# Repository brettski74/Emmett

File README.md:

# Emmett KiCad Plugin

Welcome to the Emmett Element Router - a comprehensive helper for routing heating element traces.

If you're looking for some way to control your hotplate, maybe [Milton](https://github.com/brettski74/Milton) can help.

Join us on [Discord](https://discord.gg/dnQJEGFCZ9) to meet other people interested in DIY solder reflow hotplates, ask questions, make suggestions or discuss problems. You can also raise issues here and I'll take a look when I can.

# Features

- Supports single-sided Aluminium PCB layouts.
- Includes DIY thermal fuse in the layout for safety.
- Allows resizing of the board to suit requirements.
- Performs basic thermal calculations to determine feasibility of proposed design.
- Calculates optimal resistance values based on power, temperature and voltage requirements of the hotplate.
- Optimize track geometry to achieve desired resistance value.
- Opens a dialog for entering heating element design parameters
- Allowance for process variability in copper thickness and minimum clearances.

# Requirements

- KiCad 9.0 or later
- Python 3.6+ (included with KiCad)

**NOTE: This plugin is built using the Python SWIG API for KiCad which has been deprecated by the KiCad development team. Support for the SWIG API may be removed in KiCad 10 or a later version of KiCad, at which time this plugin will cease to work as it is currently written.**

# Installing Emmett

1. Download the release ZIP file (eg. emmett-1.0.0.zip)
2. Open KiCad
3. Launch the Plugin and Content Manager
4. Click the *Install from File...* button.
5. Select the release ZIP file you downloaded (eg. emmett-1.0.0.zip)

You should now see Emmet show up among your installed plugins. When you open KiCad, you should see a new button on the tool bar for launching the Emmett dialog.

# Using Emmett

Emmett is designed to work with purpose-designed PCB layouts for heating elements. The current version only supports a single layout algorithm for an aluminium hotplate design of mine. It includes a thermal fuse which you must create on the manufactured boards for them to work and has surface mount pads for power connection. The fuse link and power connections must be soldered in place using a higher temperature solder alloy. Despite the presence of the thermal fuse and the use of higher temperature solder alloys, there is a risk that your live power connections reflow and the cables become loose. This may pose a risk of fire or equipment damage.

**It is important to ensure that your hotplate assembly includes precautions to limit the movement of the live cable ends should they become detached during a fault or other unintended modes of operation.**

You can find a hotplate layout that works with Emmett in the releases.

Load the hotplate layout.
Click the Emmett button on the toolbar to launch Emmett.

When you first open Emmett, he will analyze the currently open PCB layout to deduce some parameter values from it. On the *Technical* tab, you set most of the relevant design parameters for creating your hotplate.

## Electrical Specifications

The most likely parameters you may wish to change are the voltage and power capabilities of your power supply. These will determine the ideal resistance of the heating element on your hotplate. The *Target Resistance* will normally be calculated based on the voltage and power you provide, but you can manually enter a value if you desire.

The *Cold Current* value shows how much current will be required at ambient temperature to produce the required power in your heating element. This can give you some idea of how current constrained the design may be at low temperatures.

### Specifying Voltage and Power

Power applied to the hotplate is what matters most for achieving certain temperatures and rates of heating. You should let the thermal specifications guide the power requirements for your hotplate. If you have power to burn, you can increase the power and power margin to your heart's content, but excessive power won't really help that much. Depending on your control strategy, extremely excessive power could pose controllability problems.

Voltage is a different matter. The following advice assumes that your power supply has some way of limiting the current to safe levels regardless of the load of the current voltage and current set points. If you're power constrained, then your best bet is to specify the maximum voltage that your power supply can handle. The heating element resistance will increase with temperature. Because of this, you will be current constrained at low temperatures and voltage constrained at high temperatures. You want to take advantage of the maximum power into your hotplate at reflow temperatures because that is where the effects of thermal leakage to the ambient will be the highest and therefore you'll need the most power there to keep increasing temperature. If you are not power constrained and have the ability to vary the voltage applied to the hotplate, you may want to select a lower operating voltage. The *Cold Current* field will show the current required to reach your design power when the hotplate is at ambient temperature. Ideally you would select an operating voltage that produces a cold current value that is within the current output limits of your power supply.

## Thermal Specifications

The *Thermal Specifications* can also be tailored to your needs. All of the parameters in this section ultimately affect how much power we assume will be needed by your hotplate design to perform.

For standard tin-lead solders that melt at around 183°C, the standard temperature settings or 220°C and 25°C should be sufficient. If you're worried about tripping your thermal fuse or wear and tear on your board, you can run it at a lower temperature but unless you are seriously power constrained (eg. below 30% power margin) it is probably best to leave the maximum temperature at 220°C.

*Thermal Resistance* provides a measure of how quickly and easily your hotplate assembly loses heat to the surrounding environment. Technically, this is the thermal resistance from your hotplate assembly to the ambient environment. The lower this value, the faster heat leaks into the surrounding environment, which means that it requires more power just to resist the natural cooling from convection, conduction and radiation. This value will be estimated based on the dimensions of your hotplate. The formula used for this is somewhat speculative and based on a limited amount of empirical data. Your mileage may vary.

*Power Margin* is a somewhat arbitrary factor relating how much power you need to hold the hotplate at it's maximum temperature versus how much power is available to drive the hotplate. To heat the hotplate and its load up quickly, you need substantially more than just the holding power. A power margin of 100% is recommended. This basically sets the power requirement for your hotplate to double the holding power (ie. the holding power + 100% of the holding power on top of that). Values below about 25% may be sluggish and may struggle to reach the desired reflow temperatures in the available time unless you modify your reflow profiles to be much longer than are typical. Even at a power margin of 25-30% you may need to increase the length of your profile by 50-100% in order to give the hotplate long enough to heat up to the required temperatures to form good solder joints. 100% is a good target that should allow your hotplate to reach reflow temperatures in times comparable to standard reflow profiles.

## Track Specifications

*Minimum Spacing* sets the minimum distance between the adjacent edges of adjacent tracks - ie. the width of the non-conductive space between adjacent tracks. 0.2mm is a fairly safe and conservative value that should work for most PCB manufacturers. There's probably no need to go smaller.

*Track Thickness* sets the thickness of the copper layer that will be on your finished PCB. For 1oz copper, this should be 35µm, although it's possible that with different manufacturers or even different batches from the same manufacturer it could vary. If you've ordered PCB hotplates before, you'll know that the resistance of the manufactured PCBs does not always match the theoretical calculations. It's difficult for me to say why this is. It could be due to a variety of possible causes including a thinner than expected copper layer, etching undercut (ie. narrower than expected traces), oxidation or impurities in the copper... Who knows? Without expensive test and measurement equipment I cannot say for sure. Whatever the reason, if you're finding that the resistance of your manufactured PCB heaters is wildly different from expected, this is a parameter that you can use to adjust the calculations, spin up a new board and have that manufactured to hopefully meet your resistance expectations.

*Track Material*... It's possible that PCB hotplates could be manufactured using a conductive material other than copper. While I've given some thought to this possibility, it seems unlikely for there to be other options for DIYers at this time, so I've forgone the effort to implement support for other materials at this time. If this situation should change, maybe we can update Emmett to know about other material properties. This version explicitly uses the published values for copper.

## Track Geometry

*Track Width* is the width in millimetres of the tracks that will be created for your heating element. Narrower tracks produce higher resistances. Wider tracks produce lower resistances. Ideally, you would allow the form to calculate the optimal value for this for you based on the thermal and electrical specifications you've provided, but if you want, you can manually enter a value here instead. You do you!

*Track Spacing* is the width of the non-conductive space between adjacent edges of adjacent tracks. Ideally we want to keep this as small as possible. Wider tracks are more durable and have better thermal coupling to the underlying substrate, both of which are desirable.

*Track Pitch* is the centre to centre measurement for adjacent tracks. Track pitch is what determines how many tracks can fit within a given width on the board. It is the sum of the track width and track spacing.

## Board Extents

The *Left*, *Top*, *Right* and *Bottom* values show the position of the edges of the board as defined by the edge cuts layer on your PCB. This is determined during board analysis and the values are read-only.

*Width* and *Height* show the width and height of the layout in millimetres. This is again derived from the edge cuts layer. Width is the difference of the right and left values. Height is the difference of the bottom and top values. They are editable, but changes to these values have no effect unless you click the *Resize* button. If you wish to change the size of your hotplate, you can modify the width and height values here and then click the *Resize* button. You should see the edge cuts and mounting holes move to create a layout with your new dimensions. Doing this will also automatically trigger a re-analysis of the board layout but will not trigger regeneration of the heating element tracks.

## Electrical

This shows the calculated values of the heating element resistance at ambient temperature (ie. *Cold Resistance*) and at the maximum operating temperature (ie. *Hot Resistance*). These are calculated during board analysis and after generation of new tracks.

## Buttons

*Load* Not currently implemented. The intention was to save the parameters to a file that could be loaded again later, but board analysis seems to make this moot. i may remove these buttons in a future version. For the moment, this does nothing when clicked.

*Save* Not currently implemented. See *Load*.

*Analyze* Initiate a new analysis of the board and update the parameters accordingly. This can be used to effectively revert all the edits that have been made on the form, but only if new tracks have not already been generated. While there are some minor differences between board analysis when the form is blank and when it's not, it will mostly overwrite most changes you may have made to parameters on the form.

*Geometryze* I'm well aware that this is not a real word, but let's make it one, Damnit! *Calculate* is too vague and *Recalculate Track Geometry* is too big and cumbersome to put on a button, so Geometryze it is. As already alluded to, this will update the track width, spacing and pitch to values that should achieve the target resistance value. It currently does not take into account things like operating voltage and power. It is assumed that hotplates designed by this form will only be used for relatively low voltages and power levels. If you're planning to build a hotplate that operates above 60V or 500W, you may want to include additional design considerations not intrinsically included in the calculations on this form.

*Clear Tracks* Remove all the tracks on the PCB. Not really needed in production, because when you generate the tracks, it will do this before laying out the new tracks, anyway. This was mostly useful to me during testing and I don't see much use in removing it because I may do more development in the future. So enjoy the beauty and harmony of the extra button.

*Apply 1.21GW!* I could have called this button *Generate* or maybe even *Apply* and while that probably would have been clear enough to most users, where is the fun in that. As you may have guessed, clicking this button will clear all tracks currently on the board and lay out new heating element tracks based on the *Track Geometry* parameters currently specified. Note that this process may also move the location of the thermal fuse and power connection pads slightly in order to fit optimally between the generated tracks.

*Close* Closes the form.

# Building the Plugin

```bash
cd src
make package
```

This creates `emmett-<version>.zip` in the build directory. You can then install this using the *Install from File...* option in KiCad's Plugin and Content Manager.

# Troubleshooting

TBA...

# License

See [LICENCE.md](./LICENCE.md) for details.

# Contributing

No real guidelines as of yet, but if you have any suggestions or find any bugs feel free to create an issue against this project. Maybe take a look at existing issues to see if it's already been reported/suggested first. Also feel free to send me pull requests. I can't guarantee that I'll accept them, but they are welcome.

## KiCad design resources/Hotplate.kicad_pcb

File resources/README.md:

# Emmett Resources

Here you will find additional resources to help Emmett do his thing. At the moment, that is just a PCB layout that works with Emmett.

## Hotplate PCB Layout

The hotplate PCB layout in this directory contains the following features that are important for working with Emmett. If you are considering making a different layout, the following information may assist you in understanding what aspects of the layour are important for working with Emmett, as currently coded. Note that it is possible to implement your own track router implementation with it's own analysis and routing logic.

1. The board is assumed to be rectangular with rounded corners, formed by four straight lines and four 90° arcs. The detection of the board extents and the resize function are built on these assumptions and may not function if the edge cuts layer is formed differently.
1. The board has four mounting holes that are located near the corners. They are identified by being the only four footprints on the board with through-holes. Proper detection of the courtyard is not implemented, so the clearance radius around the holes is currently hard-coded.
1. The thermal fuse pads are assumed to be the two pads closest to the centre and are assumed to be oriented vertically to fit between the heating element traces. Courtyard detection is not implemented, so the code currently assumes a hard-coded 0.25mm courtyard around the edges of the pads.
1. The power connection pads are assumed to be placed on either side of the centre of the top edge of the board. Courtyard detection is not implemented, so the code currently assumes a hard-coded 0.25mm courtyard around the edges of the pads.
1. If you wish for text to be written onto the board containing the layout generation parameters, the code breaks the text up into three sections - mechanical, thermal and eletrical parameters. Emmett will insert this text into the first text element it finds on the board starting with *Track Width: *, *Maximum Temperature: * and *Cold Resistance: * respectively. If you place text element with that text in it, Emmett will write the generation parameters into them. They are not required. If any one of them is not found, that text will simply not be written onto the board.

## Manufacturing Considerations

The current layout is designed for use on an aluminium substrate. The board must have a thermal fuse link installed to be usable.

If you want a completely flat top, you can use countersunk M3 screws for mounting the hotplate. Ideally, this should use a 2mm aluminium plate. A 2mm plate would also be better for heat transfer, however 2mm aluminium does require a substantial price increase over the lowest price 1.6mm options available online. A 1.6mm aluminium plate may be ok for countersunk screw, but given the limited thickness of the material you will need to be very careful that you don't countersink too deeply and lose precious material for the screw head to hold on to. Don't overtighten the screws, as the 1.6mm material can deform outwards and upwards with excessive pressure from a countersunk screw. Of course, you can also use pan-head or truss-head screws which will hold the plate more securely and avoid these risks at the cost of losing an unobstructed flat top.

The most basic and low cost options include 1 W/m.K adhesive/dielectric layer between the copper traces and the aluminium substrate. This refers to the thermal conductivity of this layer. Higher numbers are better but also generally more expensive. The best materials available have a thermal conductivity of about 3 W/m.K. Better conductivity should ensure better heat transfer into the substrate and more even heating. It's as yet unclear how significant this difference may be, but given that the thermal conductivity of the aluminium substrate is somewhere in the 150-200 W/m.K and the copper traces are even higher, it's likely that this dielectric layer is the thermal bottleneck and better thermal conductivity may reduce some of the thermal stresses that could eventually lead to delamination of the traces from the substrate and eventual failure of the hotplate. If/when I have more data I will update this page on the durability differences between 1 W/m.K and 3 W/m.K dielectric adhesives.

### Soldering

The power connections and fuse link need to be soldered to the board using a high temperature solder alloy. For reflowing both tin-lead and tin-bismuth solder paste, the following solder alloys are suggested.

1. SN100C and similar alloys such as K100LD from Kester and CQ100Ge from Chipquik. These alloys are all approximately 0.7% copper and around 99.3% tin, with potentially small amounts of other materials like nickel or germanium. They have melting a melting point of 227°C which provides a nice margin above the 183°C melting point of tin-lead solder. It has generally has good flow and wetting properties and is reasonably easy to work with. This is probably your best bet, especially if your soldering skills are under-developed. It's fairly easy to find and is usually available in sizes typical for use with electronics and often with a flux core. I've even seen dollar store that was supposedly 99.3% tin and 0.7% copper and it did have the high melting point, but seemed to be a pain to work with. Maybe the extra components in the more premium brands are what's needed to improve wetting and flow, but if you can get sufficient heat and a good flux, even that dollar store stuff may work provided it has the high melting point.
1. 95-5 tin-antimony solder. This is most commonly found for use in plumbing and often as solid core wire from vendors such as Forney or Oatey more typically associated with plumbing than with electronics. It's higher melting range of 232-240°C make it better than SN100C from a thermal performance perspective, however it has poor wetting and flow characteristics that can make the formation of good solder joints difficult. I've used it very successfully for years, but it does require good heating and flux use to form good joints. If you're unfamiliar with how to identify proper wetting of the metal surfaces when soldering, you may wish to use a different alloy. It is possible to form blobs of solder around the wire that have limited fusion between the solder and the underlying copper which may lead to problems during operation. These problems may not be initially obvious but may deteriorate over time and lead to premature failure of the joint and/or the board.
1. SAC305, SAC405 and similar lead-free solder alloys. These are mostly tin with 3-4% silver and 0.5% copper and have a melting range from 217°C and 219°C. They are the most common lead-free alloy used in electronics today. While it's possible to use SAC305/405 for this purpose, the lower melting point makes it less desirable. However, it's soldering characteristics are well understood and if you already have some on-hand, it does provide an option that avoids the need to spend money on a new solder that you may have limited use for. Provided you configure your hotplate to keep the operating temperatures to levels that won't reflow your thermal fuse and power connections, it should be fine. I have formed good tin-lead solder joints on hotplates not operating above 205°C. I haven't tested a hotplate using this alloy, but in theory is can work.

Other tips:

* Use a good flux. SMD291 from Chipquik works well and is reasonably easy to clean up with low residue. I've also used Chipquik NC191 which worked, but seems less agressive than SMD291. Other reputable brands of tacky flux are probably fine also, but these are the ones I've tried that worked well enough to recommend. I've also used MG Chemicals 8342 RA rosin flux paste. It works, but leaves a lot of residue and makes clean up a pain. These solder joints will be subjected to a harsh environment. You want to give yourself the best chance of good quality joints. Avoid cheap, unidentifiable fluxes for less consequential soldering.
* Consider pre-tinning your fuse link and power connections prior to soldering onto the board. It is often easier to get good wetting with your chosen alloy and you pre-tin the wire. You are more free to apply sufficient heat and flux to the end of the wire this way and a pre-tinned wire will be easier to form a good joint than a bare wire. The same goes for the pads. Pre-tinning with your chosen alloy may make the final soldering easier and produce a higher quality joint than without pre-tinning.
* Use plenty of solder. These are relatively large pads and relatively large wires you will be soldering onto your hotplate. If you've going with the cheapest manufacturing options, you probably also have a thin layer of tin-lead solder attached to the pad. You want to dilute that as much as possible to avoid the possibility of a layer of low melting point alloy between your solder joint and the pad. Flowing plenty of solder into the joint should help achieve this. Don't go overboard, but the joint should look like a solid lump of metal when you're done, not just a thin film of solder over and between the joint components.

## Assembly

The board should be mounted in a way that allows levelling of the hotplate. A simple solution to creating four levelling legs for the hotplate can be created using some longer M3 screws, M3 nuts and some F-F M3 metal stand-offs. Something like a socket-head cap screws are ideal as they provide a relatively flat head that can work ok as a foot. Wind a nut onto the cap screw a reasonable way along the thread. Then screw the cap screw into one end of a stand-off. The other end of the stand-off gets screwed to the hotplate using some shorter screws of your choosing. You can adjust the height of the leg by screwing the cap screw more or less into the bottom of the stand-off. Once you have the height where you need it, you can tighten up the nut against the stand-off to lock it in place. It's a good idea to include washers where you secure the hotplate to the stand-off to spread the load onto more of the aluminium substrate.

Tip: If you're having trouble finding a spanner to fit onto typical M3 hex stand-offs, try a 3/16". Go figure!

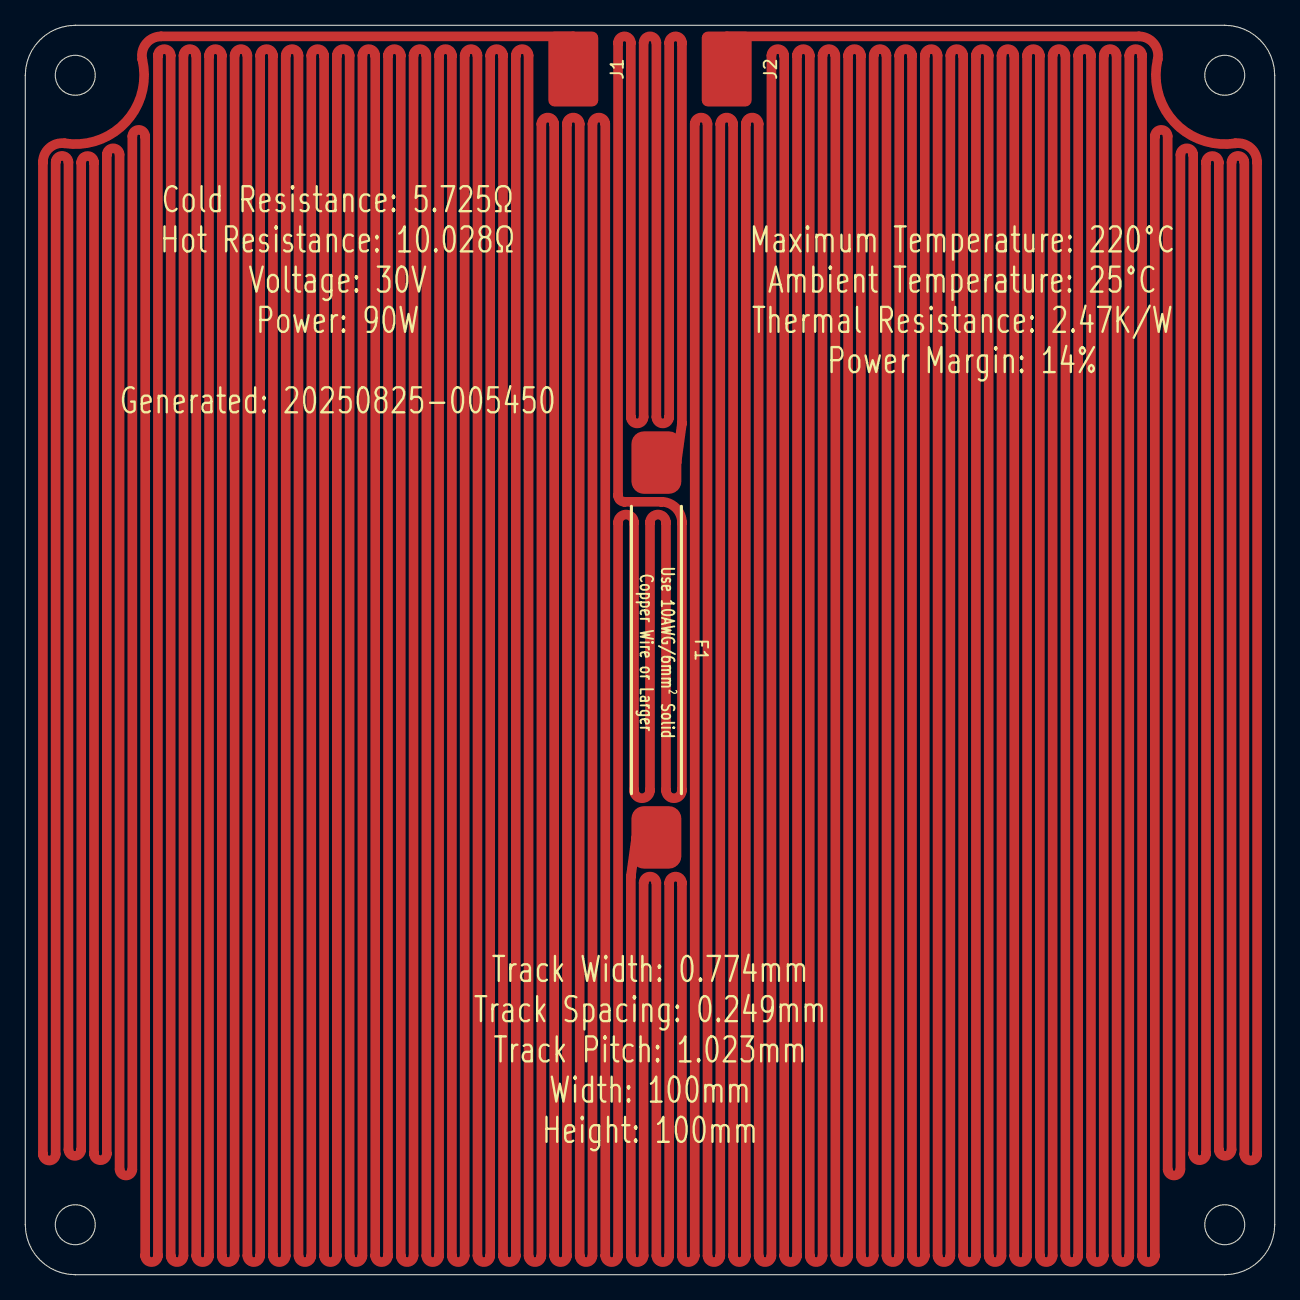
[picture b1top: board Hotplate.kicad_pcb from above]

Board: 2 copper layers, 100.0 x 100.0 mm, 3 parts (0 on the bottom side), 2 nets.

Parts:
F1: Thermal Fuse, SN100C, Front, 35mm
J1, J2: Hotplate_Power_Connection; SMD_PowerConnection_4x6mm

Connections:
unnamed: F1.1, J1.1
unnamed: F1.2, J2.1

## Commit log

2025-08-10 Initial commit.
2025-08-10 Builds a working zip plugin package that can be loaded in the Plugin and Content Manager.
2025-08-10 Ignore the build directory.
2025-08-12 Implemented resistance calculator class.
2025-08-12 First stab at board_analyzer class. We'll see if it works...
2025-08-12 Fixing GPT5's stupid, brain-dead, moronic hacks that broke my Makefile.
2025-08-12 Proof of concept resistance calculation message box pops up.
2025-08-14 Initial board_builder class with clear and add tracks.
2025-08-15 Simple serpentine trace pattern implemented.
2025-08-16 al_track_router doing basic track routing for Al PCB heaters, but not doing board analysis and pad placement, yet.
2025-08-16 Al track routing working - moves pad to correct location and routes tracks around them. No form integration yet.
2025-08-17 Track Geometry fields now working.
2025-08-17 Tooltips on all the form controls.
2025-08-17 Board resize now works.
2025-08-17 Modified Al track router to route tracks in between the fuse pads vertically instead of horizontally to avoid potential challenges with discontinuities during optimization.
2025-08-18 Track width optimization kinda works, but slight variance between offline and online resistance calculations that requires investigation.
2025-08-18 Added cold current field to show potential for current limiting on the lower end.
2025-08-18 Updated README and moved to base directory. Added cold resistance calculation.
2025-08-18 Minor README updates.
2025-08-18 Fixed emmett-technical-tab.png filename
2025-08-18 Added LICENCE
2025-08-18 Write generation parameters onto board and parse text during analysis to get a better set of analysis parameters values.
2025-08-19 Added a README for the resources directory.
2025-08-21 Optimization bug-fixes. UI and analysis enhancements. Refactor optimization into TrackRouter base class.
2025-08-26 Updates based on test results from first Al PCB samples from JLCPCB.
2025-08-26 Added field to automatically regenerate the geometry when clicking the apply button. Defaults to true.
2025-08-26 Missed saving autogenerate geometry flag default in fbp file.
2025-09-02 Updated README with links to Milton and Discord.
2025-09-14 Set version to 0.1b
2025-09-14 Ensure that track thickness is applied to new resistance calculations. Disabled debug ready for release.
2026-01-18 Basic trace layout working.
2026-01-19 Close small gap at the centre of the board.
2026-01-19 Added board margin detection and configuration.
2026-01-21 Modify mask for bootstrap jumper to use two separate inset arcs to avoid edge effects.
2026-01-21 Cleaned up debug.
2026-01-25 Ensure track count is even to fix occasional layout bugs.
2026-01-25 Fixed layout generation failures in the original Al trace router.
2026-01-25 Fixed bugbot issues prior to PR merge.
2026-01-25 Added missing case for avoid_pad.
2026-01-25 Fixed remaining BugBot issues.
2026-01-25 Fix overcalculation of track pitch during track optimization.
2026-01-25 Removed duplicate import.
2026-01-25 Updated release metadata information for new release.
